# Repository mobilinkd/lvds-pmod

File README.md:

# 2m QSD PMOD

The board is designed for experimenting with an all-digital SERDES-based
quadrature sampling detector (QSD) and quadrature modulator.

This is a PMOD for differential (balanced) to/from single-ended (unbalanced)
I/O.  It has a 4:1 balun to match the 200 Ohm impedance of the PMOD to the
50 Ohm SMA.

The center tap on the balun is biased at VDD/2.

The board includes a 4-pole band-pass filter centered around the 2m amateur
radio band.  It is a Chebyshev filter with 1dB ripple in the passband. It is
designed to both be an anti-aliasing filter and to suppress the commercial
FM radio band.

This repo contains KiCAD files and Gerbers for those wanting to make their
own boards.

An [interactive BOM](bom/ibom-2m%20QSD%20PMOD-A.html) is available.

This project is OSHW (Open Source Hardware), released under the GPLv3 license.

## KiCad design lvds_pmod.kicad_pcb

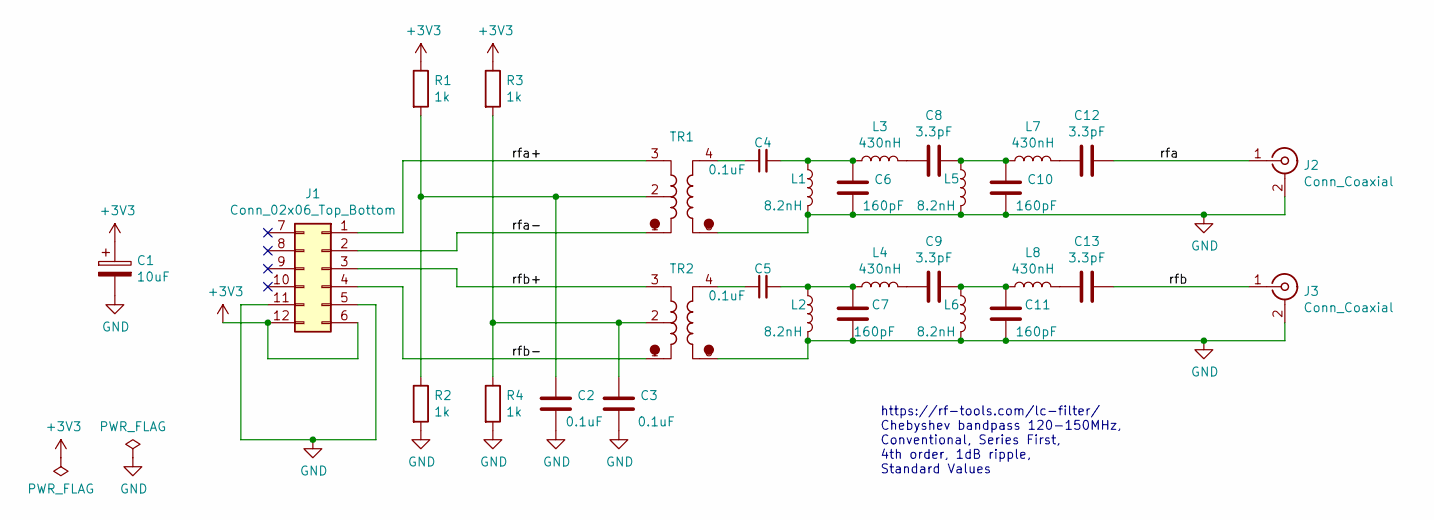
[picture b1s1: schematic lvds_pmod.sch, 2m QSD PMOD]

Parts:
C1: 10uF; CP_EIA-3216-12_Kemet-S_Pad1.58x1.35mm_HandSolder
C2, C3: 0.1uF; C_0603_1608Metric_Pad1.08x0.95mm_HandSolder
C4, C5: 0.1uF; C_0603_1608Metric
C6, C7, C10, C11: 160pF; C_0603_1608Metric_Pad1.08x0.95mm_HandSolder
C8, C9, C12, C13: 3.3pF; C_0603_1608Metric_Pad1.08x0.95mm_HandSolder
J1: Conn_02x06_Top_Bottom; PinHeader_2x06_P2.54mm_Horizontal
J2, J3: Conn_Coaxial; SMA_Amphenol_901-144_Vertical
L1, L2, L5, L6: 8.2nH; L_0603_1608Metric_Pad1.05x0.95mm_HandSolder
L3, L4, L7, L8: 430nH; L_0603_1608Metric_Pad1.05x0.95mm_HandSolder
R1, R2, R3, R4: 1k; R_0603_1608Metric_Pad0.98x0.95mm_HandSolder
TR1, TR2: CX2047LNL; XFMR_TC1-1-13M+

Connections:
+3V3: C1.1, J1.6, J1.12, R1.1, R3.1
/rfa: C12.1, J2.1 (In)
/rfa+: J1.1, TR1.3
/rfa-: J1.2, TR1.1
/rfb: C13.1, J3.1 (In)
/rfb+: J1.3, TR2.3
/rfb-: J1.4, TR2.1
GND: C1.2, C2.2, C3.2, C6.2, C7.2, C10.2, C11.2, J1.5, J1.11, J2.2 (Ext), J3.2 (Ext), L1.2, L2.2, L5.2, L6.2, R2.2, R4.2, TR1.6, TR2.6
unnamed: C2.1, R1.2, R2.1, TR1.2
unnamed: C3.1, R3.2, R4.1, TR2.2
unnamed: C4.1, TR1.4
unnamed: C4.2, C6.1, L1.1, L3.1
unnamed: C5.1, TR2.4
unnamed: C5.2, C7.1, L2.1, L4.1
unnamed: C8.2, L3.2
unnamed: C9.2, L4.2
unnamed: C8.1, C10.1, L5.1, L7.1
unnamed: C9.1, C11.1, L6.1, L8.1
unnamed: C12.2, L7.2
unnamed: C13.2, L8.2

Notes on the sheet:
https://rf-tools.com/lc-filter/ Chebyshev bandpass 120-150MHz, Conventional, Series First, 4th order, 1dB ripple, Standard Values

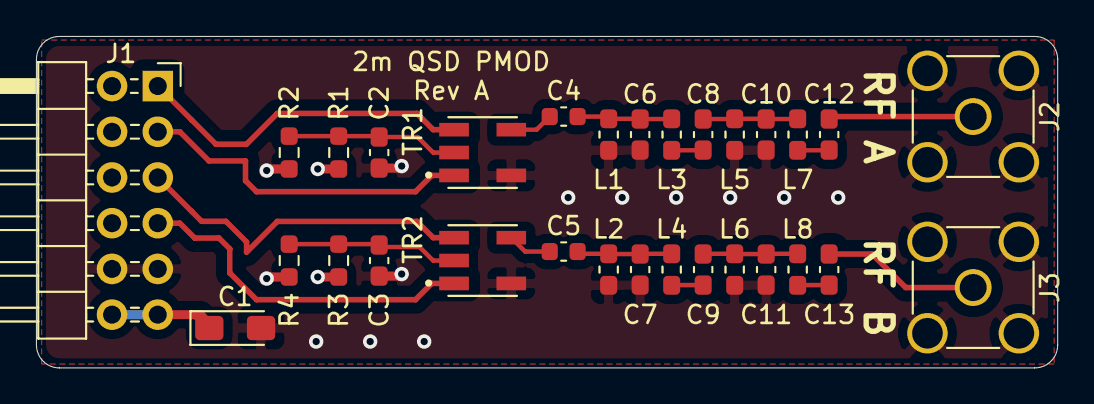
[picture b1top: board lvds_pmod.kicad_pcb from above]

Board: 4 copper layers, 56.7 x 18.4 mm, 31 parts (1 on the bottom side), 20 nets.

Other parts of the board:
G1: LOGO; Mobilinkd_Logo

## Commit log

2021-10-10 Initial commit.
2021-10-21 Add interactive BOM.
2021-10-21 Add link to iBOM.
